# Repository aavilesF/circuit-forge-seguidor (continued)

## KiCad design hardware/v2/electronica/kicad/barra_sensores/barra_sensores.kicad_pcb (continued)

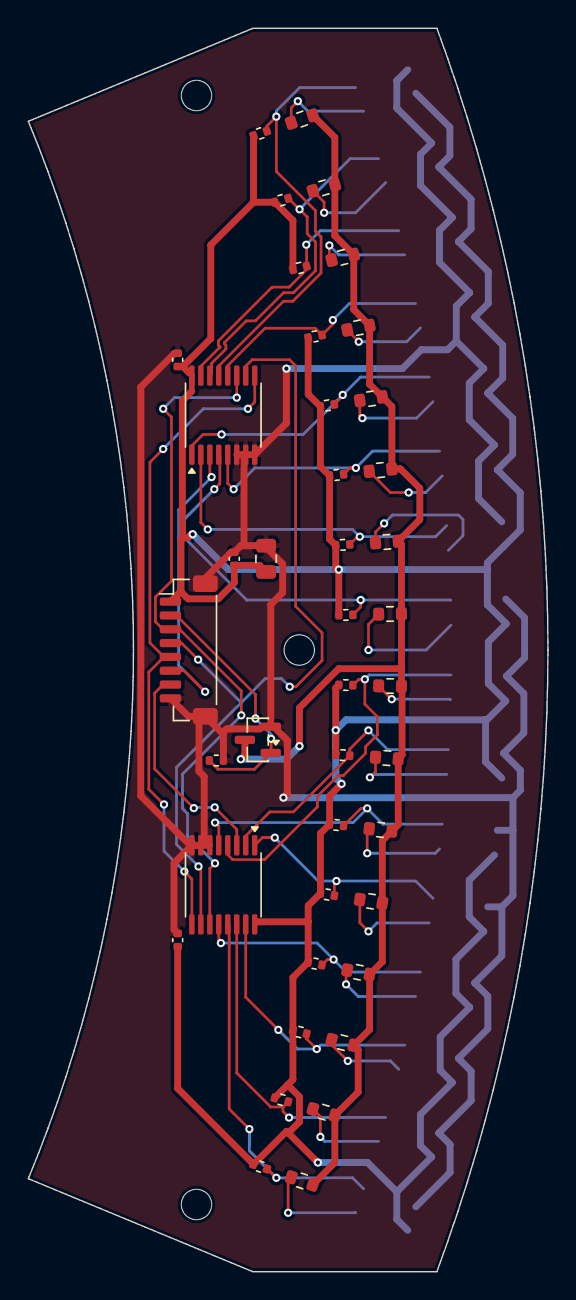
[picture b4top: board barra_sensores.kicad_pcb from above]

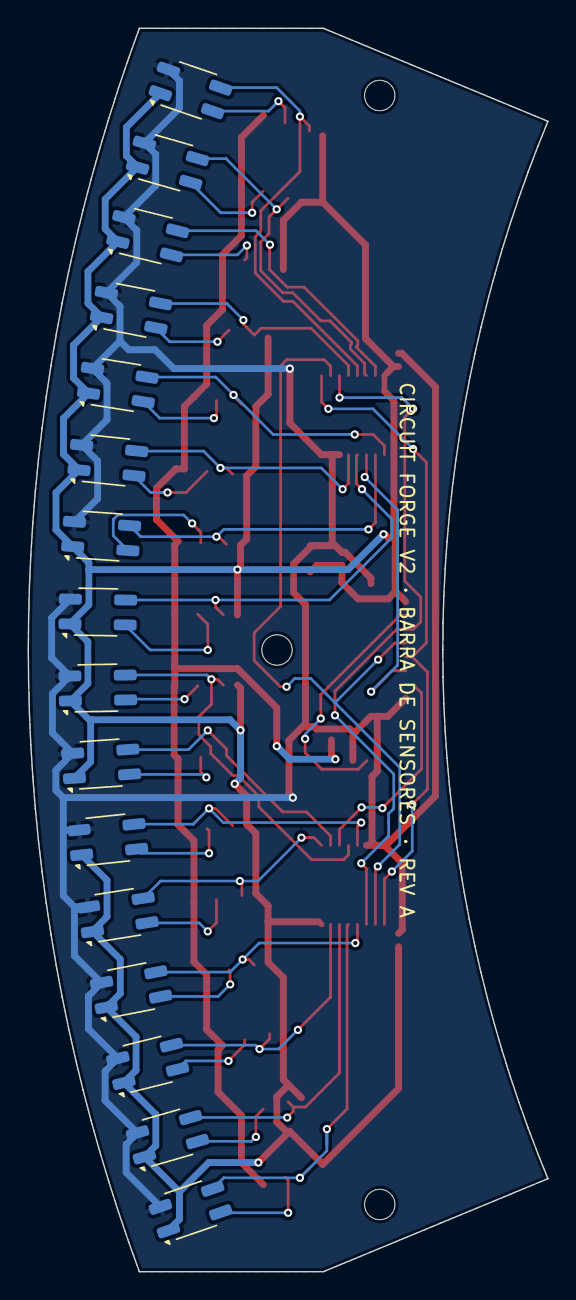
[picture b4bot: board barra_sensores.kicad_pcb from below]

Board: 2 copper layers, 37.6 x 90.0 mm, 60 parts (16 on the bottom side), 41 nets.

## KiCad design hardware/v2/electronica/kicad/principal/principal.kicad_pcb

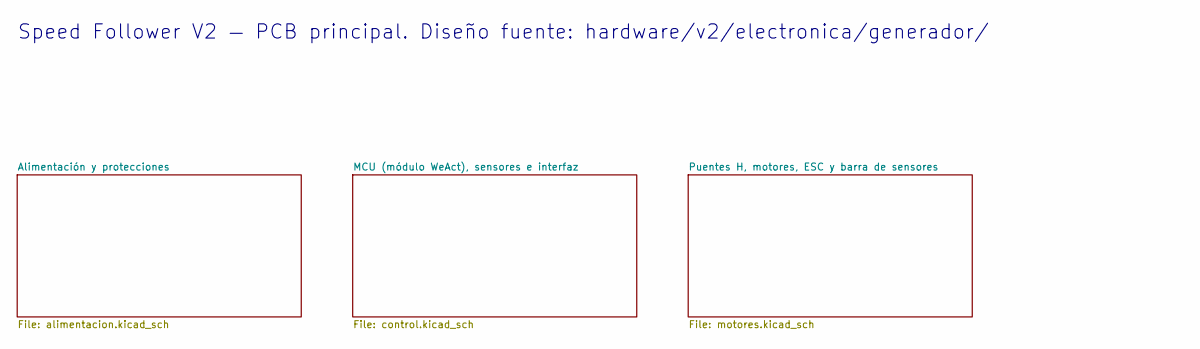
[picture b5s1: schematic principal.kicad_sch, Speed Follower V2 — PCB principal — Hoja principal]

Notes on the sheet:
Speed Follower V2 — PCB principal. Diseño fuente: hardware/v2/electronica/generador/

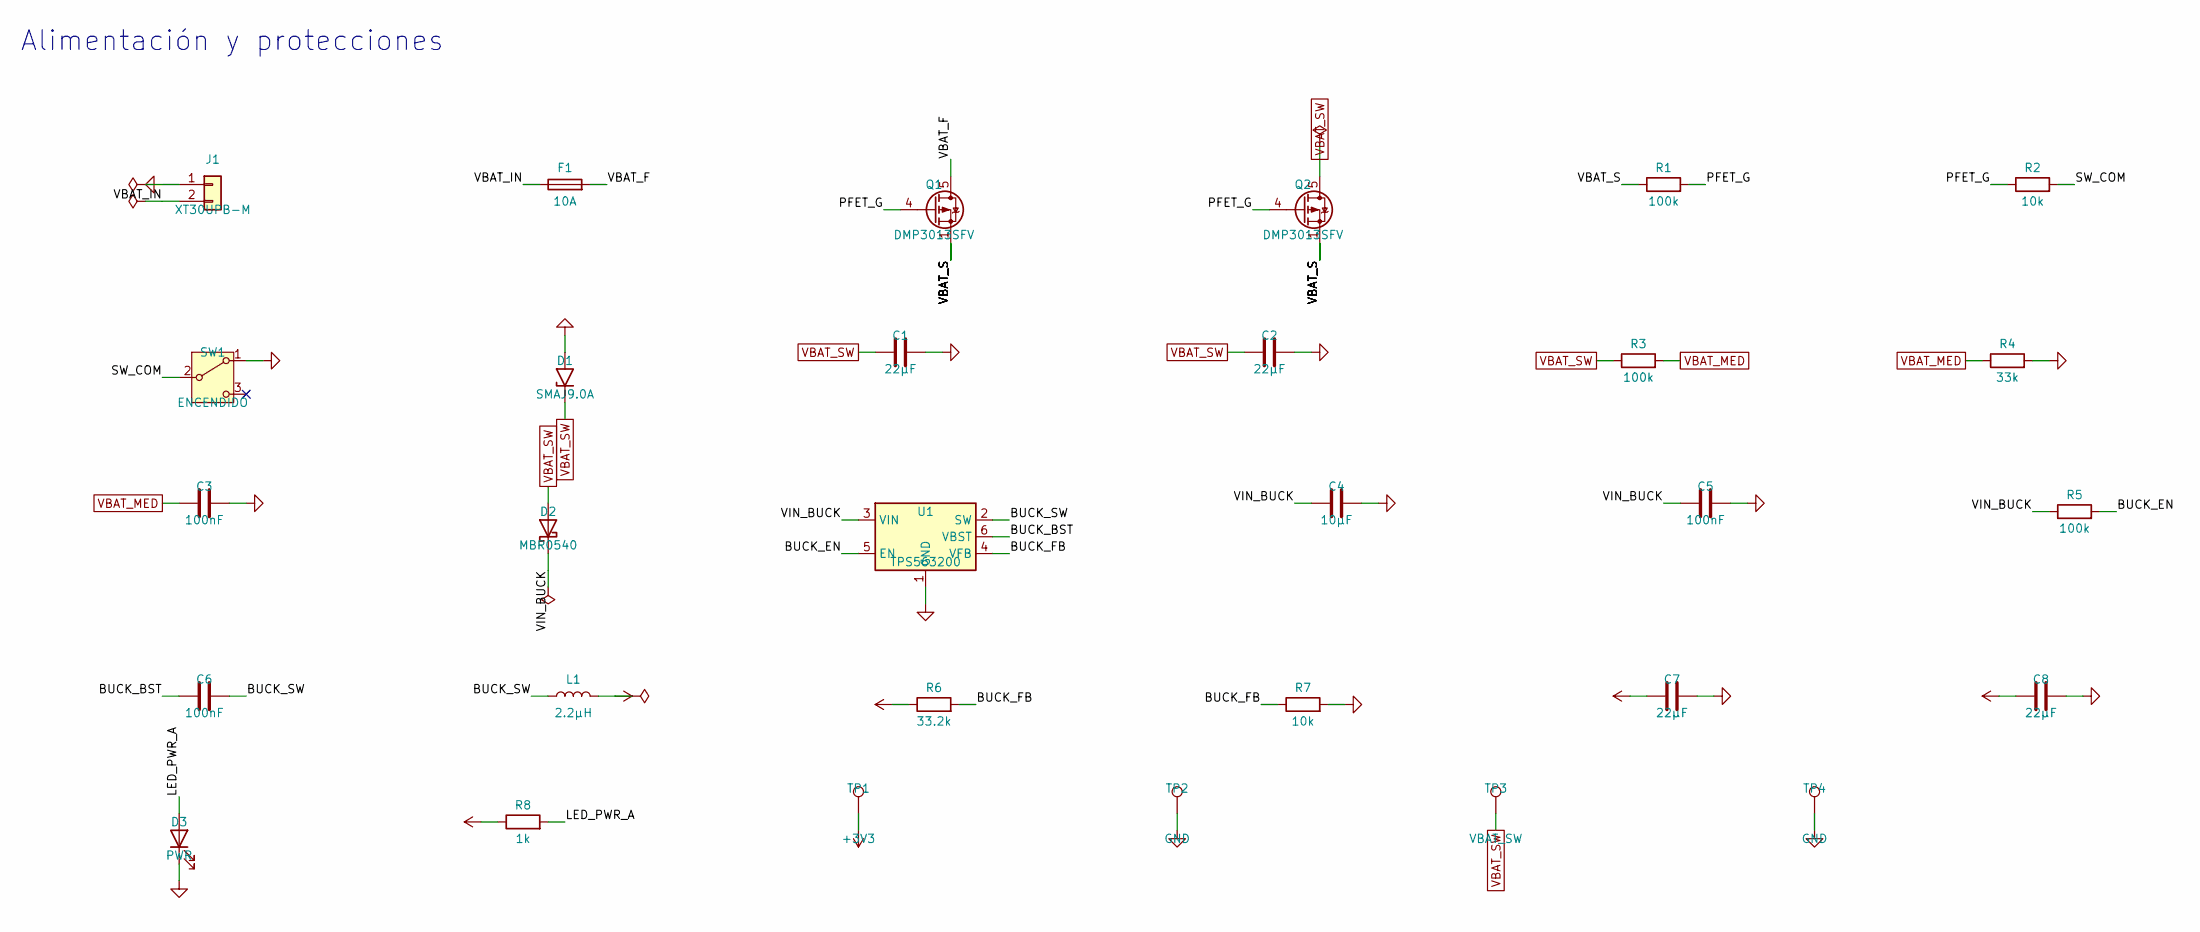
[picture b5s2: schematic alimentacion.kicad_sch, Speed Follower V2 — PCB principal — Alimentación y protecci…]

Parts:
C1, C2, C7, C8: 22µF; C_0805_2012Metric; MPN GRM21BR61E226ME44L
C3, C5, C6: 100nF; C_0402_1005Metric; MPN GRM155R71C104KA88D
C4: 10µF; C_0805_2012Metric; MPN GRM21BR61E106KA73L
D1: SMAJ9.0A; D_SMA; MPN SMAJ9.0A
D2: MBR0540; D_SOD-123; MPN MBR0540T1G
D3: PWR; LED_0603_1608Metric; MPN APT1608SGC
F1: 10A; Fuse_Blade_Mini_directSolder; MPN 0297010.WXNV
J1: XT30UPB-M; AMASS_XT30UPB-M_1x02_P5.0mm_Vertical; MPN XT30UPB-M
L1: 2.2µH; L_Wuerth_MAPI-4030; MPN 74438357022
Q1, Q2: DMP3013SFV; Diodes_PowerDI3333-8; MPN DMP3013SFV-7
R1, R3, R5: 100k; R_0402_1005Metric; MPN RC0402FR-07100KL
R2, R7: 10k; R_0402_1005Metric; MPN RC0402FR-0710KL
R4: 33k; R_0402_1005Metric; MPN RC0402FR-0733KL
R6: 33.2k; R_0402_1005Metric; MPN RC0402FR-0733K2L
R8: 1k; R_0402_1005Metric; MPN RC0402FR-071KL
SW1: ENCENDIDO; SW_Slide_SPDT_Angled_CK_OS102011MA1Q; MPN OS102011MA1QN1
TP1: +3V3; TestPoint_Pad_D1.0mm; MPN —
TP2, TP4: GND; TestPoint_Pad_D1.0mm; MPN —
TP3: VBAT_SW; TestPoint_Pad_D1.0mm; MPN —
U1: TPS563200; SOT-23-6; MPN TPS563200DDCR

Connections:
+3V3: C7.1, C8.1, L1.2, R6.1, R8.1, TP1.1; also elsewhere on the board
/Alimentación y protecciones/BUCK_BST: C6.1, U1.6 (VBST)
/Alimentación y protecciones/BUCK_EN: R5.2, U1.5 (EN)
/Alimentación y protecciones/BUCK_FB: R6.2, R7.1, U1.4 (VFB)
/Alimentación y protecciones/BUCK_SW: C6.2, L1.1, U1.2 (SW)
/Alimentación y protecciones/LED_PWR_A: D3.2 (A), R8.2
/Alimentación y protecciones/PFET_G: Q1.4 (G), Q2.4 (G), R1.2, R2.1
/Alimentación y protecciones/SW_COM: R2.2, SW1.2 (B)
/Alimentación y protecciones/VBAT_F: F1.2, Q1.5 (D)
/Alimentación y protecciones/VBAT_IN: F1.1, J1.2
/Alimentación y protecciones/VBAT_S: Q1.1 (S), Q1.2 (S), Q1.3 (S), Q2.1 (S), Q2.2 (S), Q2.3 (S), R1.1
/Alimentación y protecciones/VIN_BUCK: C4.1, C5.1, D2.1 (K), R5.1, U1.3 (VIN)
GND: C1.2, C2.2, C3.2, C4.2, C5.2, C7.2, C8.2, D1.2 (A2), D3.1 (K), J1.1, R4.2, R7.2, SW1.1 (A), TP2.1, TP4.1, U1.1 (GND); also elsewhere on the board
VBAT_MED: C3.1, R3.2, R4.1; also elsewhere on the board
VBAT_SW: C1.1, C2.1, D1.1 (A1), D2.2 (A), Q2.5 (D), R3.1, TP3.1; also elsewhere on the board

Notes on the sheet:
Alimentación y protecciones

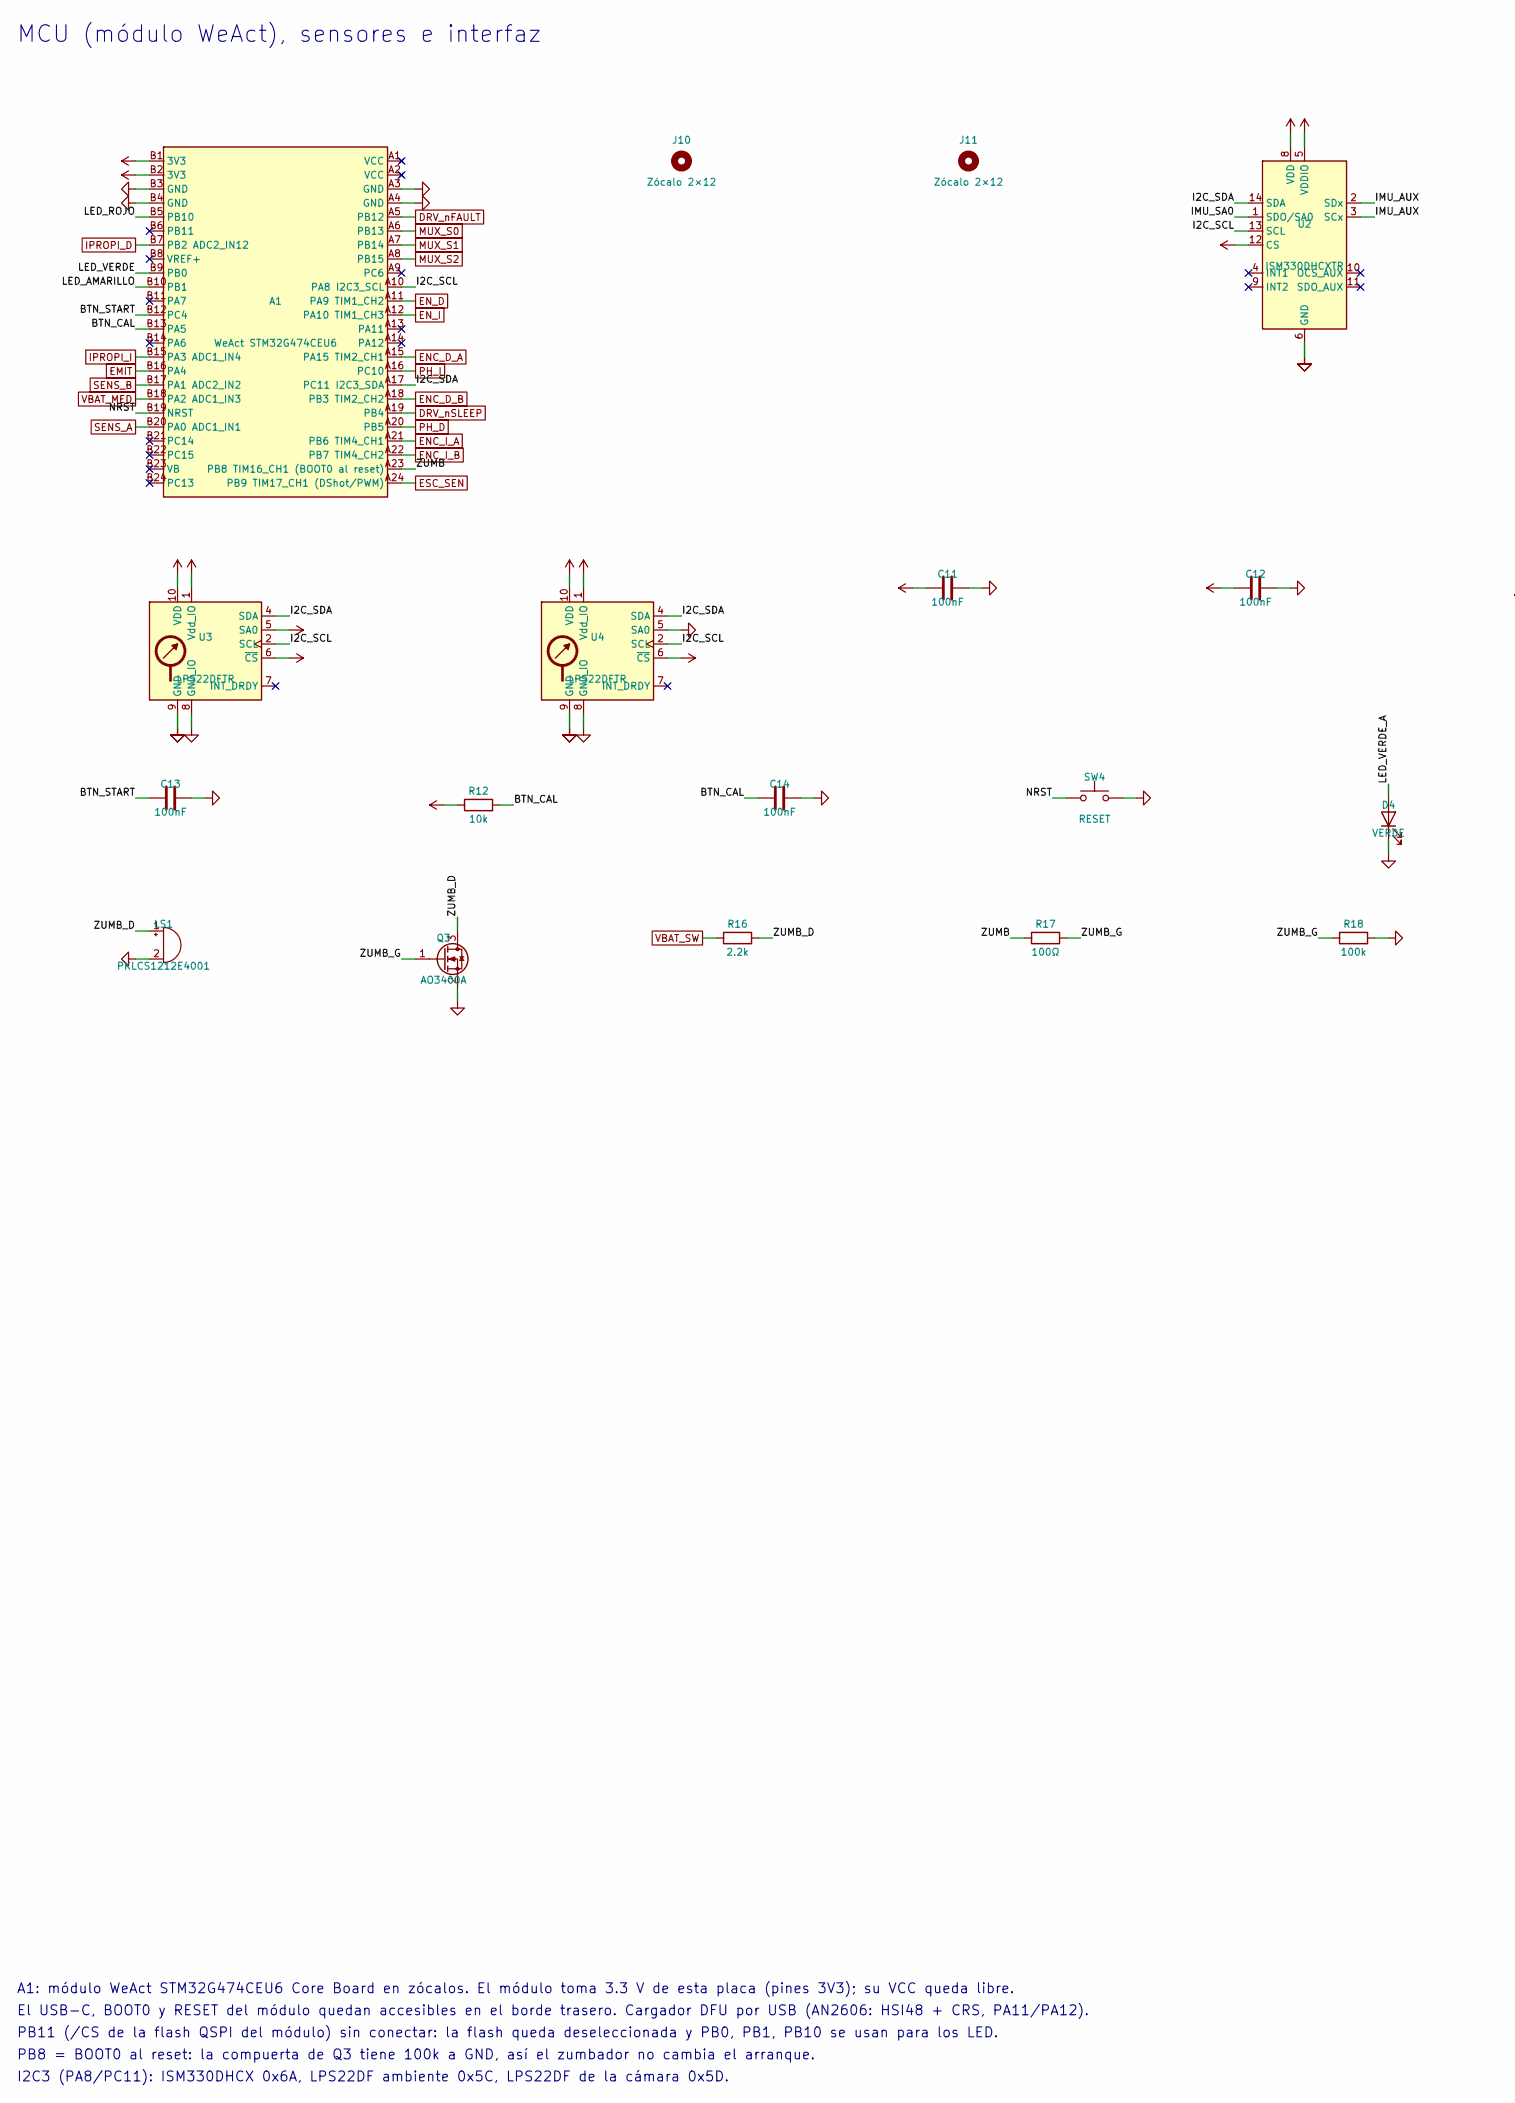
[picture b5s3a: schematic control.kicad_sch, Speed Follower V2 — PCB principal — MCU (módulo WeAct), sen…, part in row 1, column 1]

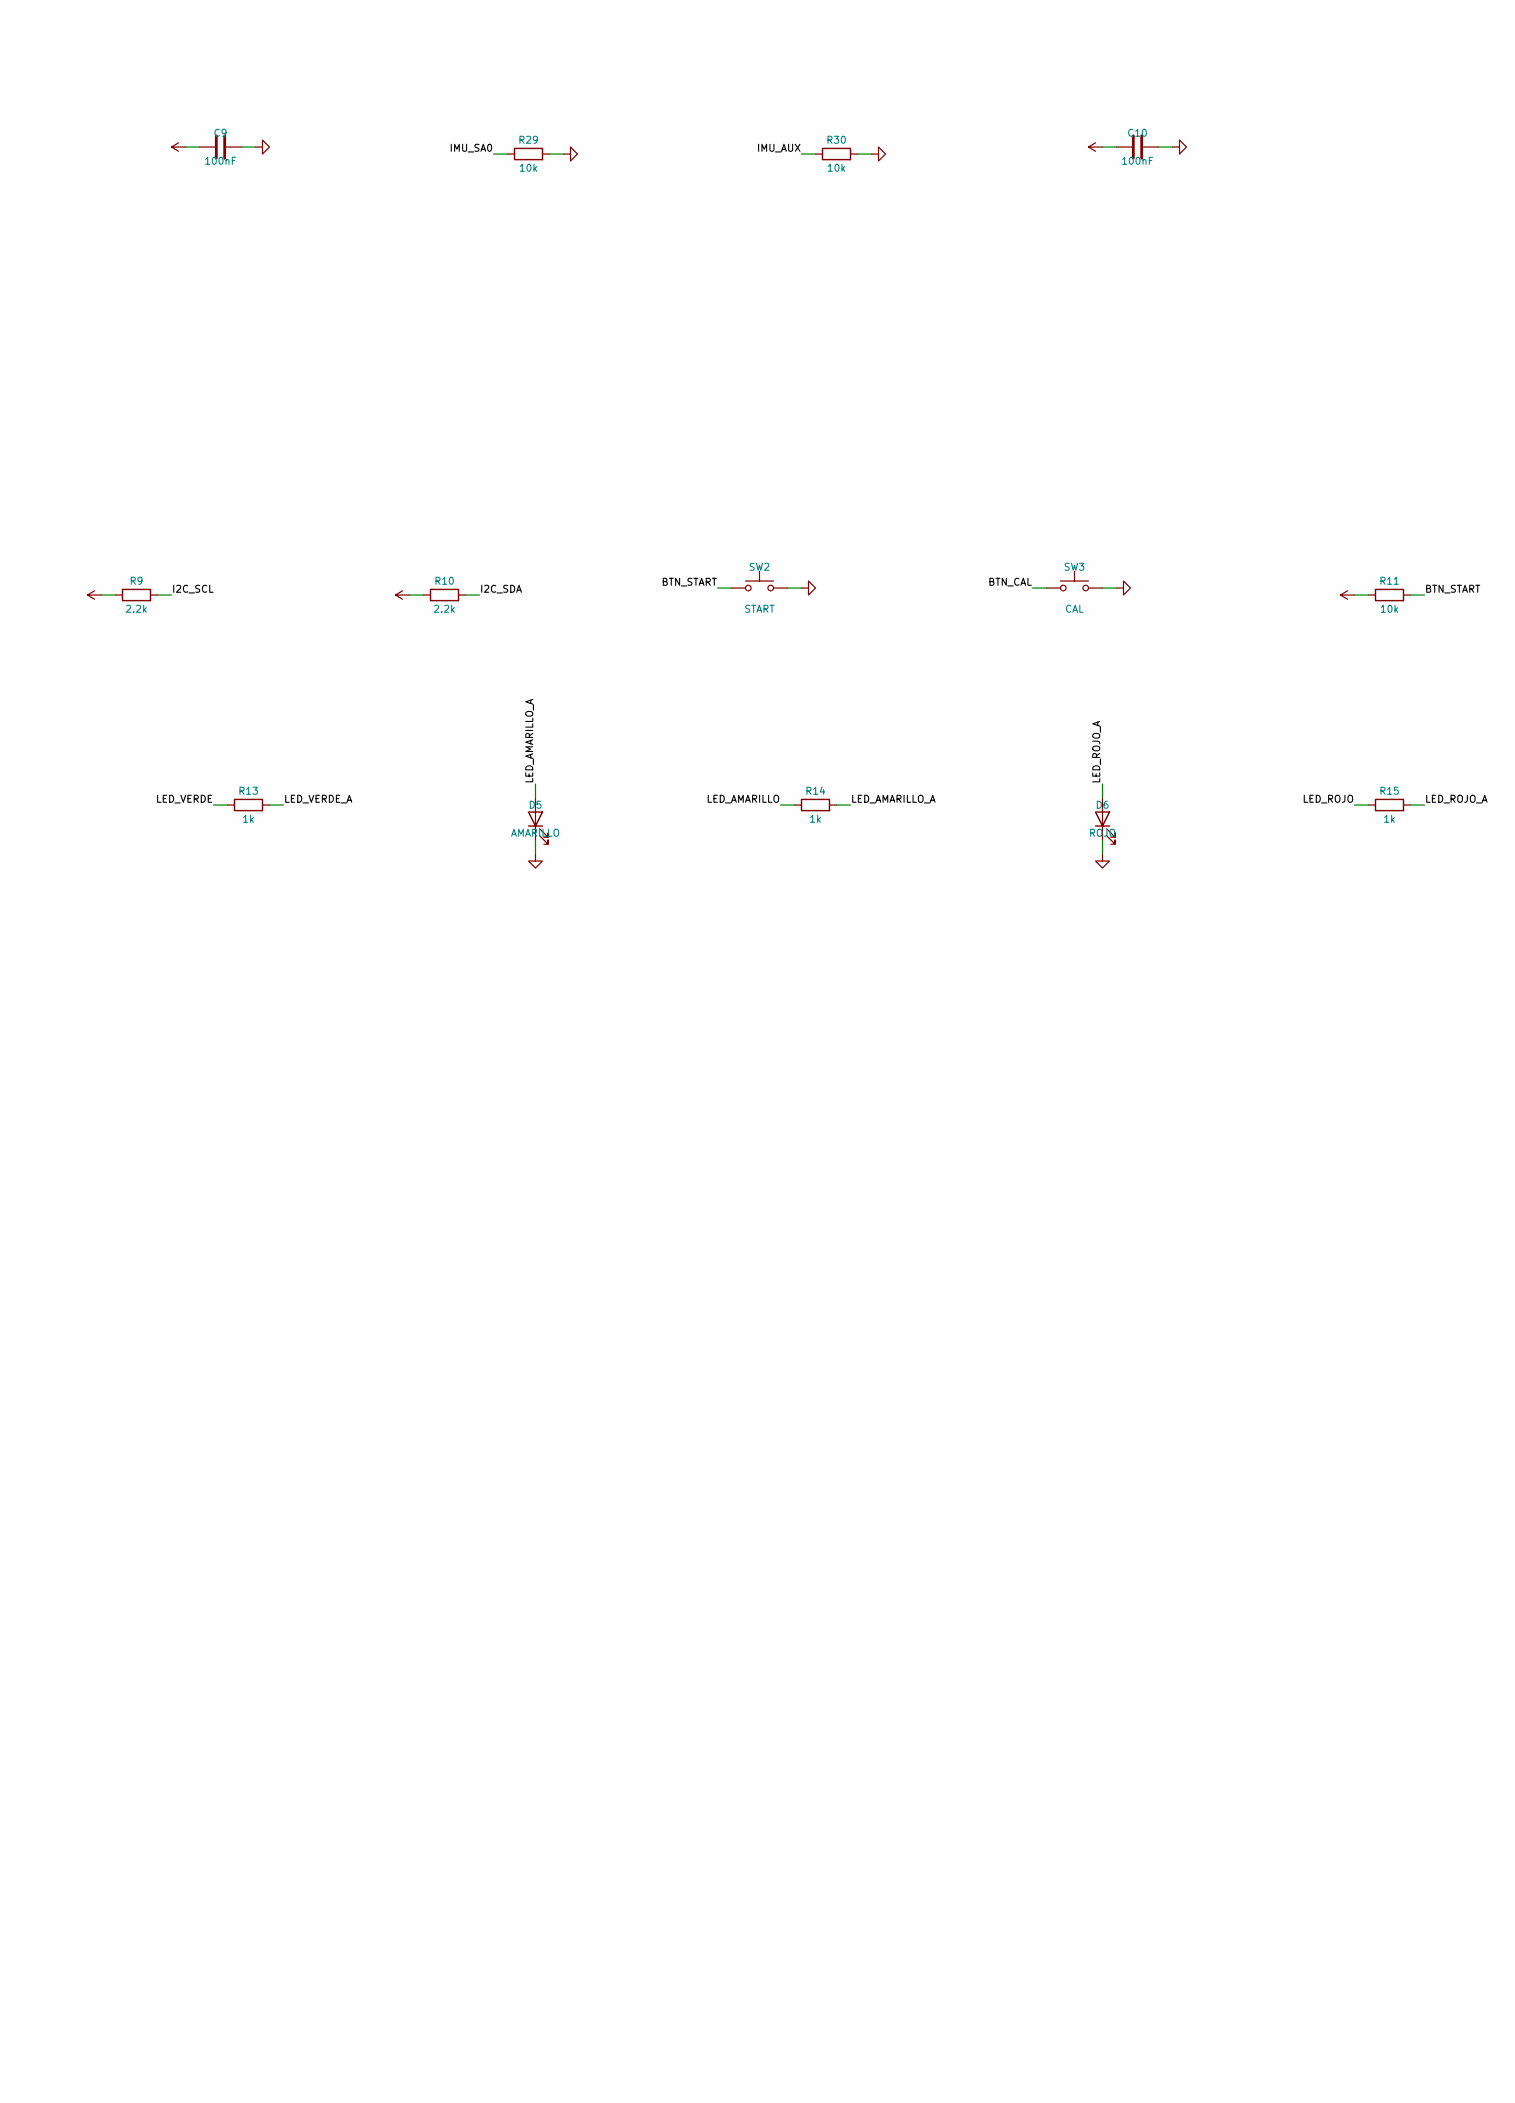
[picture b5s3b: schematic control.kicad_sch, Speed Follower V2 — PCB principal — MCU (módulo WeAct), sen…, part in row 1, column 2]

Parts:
A1: WeAct STM32G474CEU6; WeAct_STM32G474_CoreBoard_Zocalo; MPN STM32G474CEU6 Core Board V1.0
C9, C10, C11, C12, C13, C14: 100nF; C_0402_1005Metric; MPN GRM155R71C104KA88D
D4: VERDE; LED_0603_1608Metric; MPN APT1608SGC
D5: AMARILLO; LED_0603_1608Metric; MPN APT1608YC
D6: ROJO; LED_0603_1608Metric; MPN APT1608EC
J10, J11: Zócalo 2×12; MPN Zócalo hembra 2×12, paso 2.54 mm, 8.5 m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
LS1: PKLCS1212E4001; Buzzer_Murata_PKLCS1212E; MPN PKLCS1212E4001-R1
Q3: AO3400A; SOT-23; MPN AO3400A
R9, R10, R16: 2.2k; R_0402_1005Metric; MPN RC0402FR-072K2L
R11, R12, R29, R30: 10k; R_0402_1005Metric; MPN RC0402FR-0710KL
R13, R14, R15: 1k; R_0402_1005Metric; MPN RC0402FR-071KL
R17: 100Ω; R_0402_1005Metric; MPN RC0402FR-07100RL
R18: 100k; R_0402_1005Metric; MPN RC0402FR-07100KL
SW2: START; SW_SPST_Omron_B3FS-100xP; MPN B3FS-1000P
SW3: CAL; SW_SPST_Omron_B3FS-100xP; MPN B3FS-1000P
SW4: RESET; SW_SPST_B3U-1000P; MPN B3U-1000P
U2: ISM330DHCXTR; LGA-14_3x2.5mm_P0.5mm_LayoutBorder3x4y; MPN ISM330DHCXTR
U3, U4: LPS22DFTR; ST_HLGA-10_2x2mm_P0.5mm_LayoutBorder3x2y; MPN LPS22DFTR

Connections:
+3V3: A1.B1 (3V3), A1.B2 (3V3), C9.1, C10.1, C11.1, C12.1, R9.1, R10.1, R11.1, R12.1, U2.5 (VDDIO), U2.8 (VDD), U2.12 (CS), U3.1 (Vdd_IO), U3.5 (SA0), U3.6 (~CS), U3.10 (VDD), U4.1 (Vdd_IO), U4.6 (~CS), U4.10 (VDD); also elsewhere on the board
/MCU (módulo WeAct), sensores e interfaz/BTN_CAL: A1.B13 (PA5), C14.1, R12.2, SW3.1
/MCU (módulo WeAct), sensores e interfaz/BTN_START: A1.B12 (PC4), C13.1, R11.2, SW2.1
/MCU (módulo WeAct), sensores e interfaz/I2C_SCL: A1.A10 (PA8 I2C3_SCL), R9.2, U2.13 (SCL), U3.2 (SCL), U4.2 (SCL)
/MCU (módulo WeAct), sensores e interfaz/I2C_SDA: A1.A17 (PC11 I2C3_SDA), R10.2, U2.14 (SDA), U3.4 (SDA), U4.4 (SDA)
/MCU (módulo WeAct), sensores e interfaz/IMU_AUX: R30.1, U2.2 (SDx), U2.3 (SCx)
/MCU (módulo WeAct), sensores e interfaz/IMU_SA0: R29.1, U2.1 (SDO/SA0)
/MCU (módulo WeAct), sensores e interfaz/LED_AMARILLO: A1.B10 (PB1), R14.1
/MCU (módulo WeAct), sensores e interfaz/LED_AMARILLO_A: D5.2 (A), R14.2
/MCU (módulo WeAct), sensores e interfaz/LED_ROJO: A1.B5 (PB10), R15.1
/MCU (módulo WeAct), sensores e interfaz/LED_ROJO_A: D6.2 (A), R15.2
/MCU (módulo WeAct), sensores e interfaz/LED_VERDE: A1.B9 (PB0), R13.1
/MCU (módulo WeAct), sensores e interfaz/LED_VERDE_A: D4.2 (A), R13.2
/MCU (módulo WeAct), sensores e interfaz/NRST: A1.B19 (NRST), SW4.1
/MCU (módulo WeAct), sensores e interfaz/ZUMB: A1.A23 (PB8 TIM16_CH1 (BOOT0 al reset)), R17.1
/MCU (módulo WeAct), sensores e interfaz/ZUMB_D: LS1.1 (+), Q3.3 (D), R16.2
/MCU (módulo WeAct), sensores e interfaz/ZUMB_G: Q3.1 (G), R17.2, R18.1
DRV_nFAULT: A1.A5 (PB12); also elsewhere on the board
DRV_nSLEEP: A1.A19 (PB4); also elsewhere on the board
EMIT: A1.B16 (PA4); also elsewhere on the board
ENC_D_A: A1.A15 (PA15 TIM2_CH1); also elsewhere on the board
ENC_D_B: A1.A18 (PB3 TIM2_CH2); also elsewhere on the board
ENC_I_A: A1.A21 (PB6 TIM4_CH1); also elsewhere on the board
ENC_I_B: A1.A22 (PB7 TIM4_CH2); also elsewhere on the board
EN_D: A1.A11 (PA9 TIM1_CH2); also elsewhere on the board
EN_I: A1.A12 (PA10 TIM1_CH3); also elsewhere on the board
ESC_SEN: A1.A24 (PB9 TIM17_CH1 (DShot/PWM)); also elsewhere on the board
GND: A1.A3 (GND), A1.A4 (GND), A1.B3 (GND), A1.B4 (GND), C9.2, C10.2, C11.2, C12.2, C13.2, C14.2, D4.1 (K), D5.1 (K), D6.1 (K), LS1.2 (-), Q3.2 (S), R18.2, R29.2, R30.2, SW2.2, SW3.2, SW4.2, U2.6 (GND), U2.7 (GND), U3.3 (GND), U3.8 (GND_IO), U3.9 (GND), U4.3 (GND), U4.5 (SA0), U4.8 (GND_IO), U4.9 (GND); also elsewhere on the board
IPROPI_D: A1.B7 (PB2 ADC2_IN12); also elsewhere on the board
IPROPI_I: A1.B15 (PA3 ADC1_IN4); also elsewhere on the board
MUX_S0: A1.A6 (PB13); also elsewhere on the board
MUX_S1: A1.A7 (PB14); also elsewhere on the board
MUX_S2: A1.A8 (PB15); also elsewhere on the board
PH_D: A1.A20 (PB5); also elsewhere on the board
PH_I: A1.A16 (PC10); also elsewhere on the board
SENS_A: A1.B20 (PA0 ADC1_IN1); also elsewhere on the board
SENS_B: A1.B17 (PA1 ADC2_IN2); also elsewhere on the board
VBAT_MED: A1.B18 (PA2 ADC1_IN3); also elsewhere on the board
VBAT_SW: R16.1; also elsewhere on the board

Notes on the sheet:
MCU (módulo WeAct), sensores e interfaz
A1: módulo WeAct STM32G474CEU6 Core Board en zócalos. El módulo toma 3.3 V de esta placa (pines 3V3); su VCC queda libre.
El USB-C, BOOT0 y RESET del módulo quedan accesibles en el borde trasero. Cargador DFU por USB (AN2606: HSI48 + CRS, PA11/PA12).
PB11 (/CS de la flash QSPI del módulo) sin conectar: la flash queda deseleccionada y PB0, PB1, PB10 se usan para los LED.
PB8 = BOOT0 al reset: la compuerta de Q3 tiene 100k a GND, así el zumbador no cambia el arranque.
I2C3 (PA8/PC11): ISM330DHCX 0x6A, LPS22DF ambiente 0x5C, LPS22DF de la cámara 0x5D.

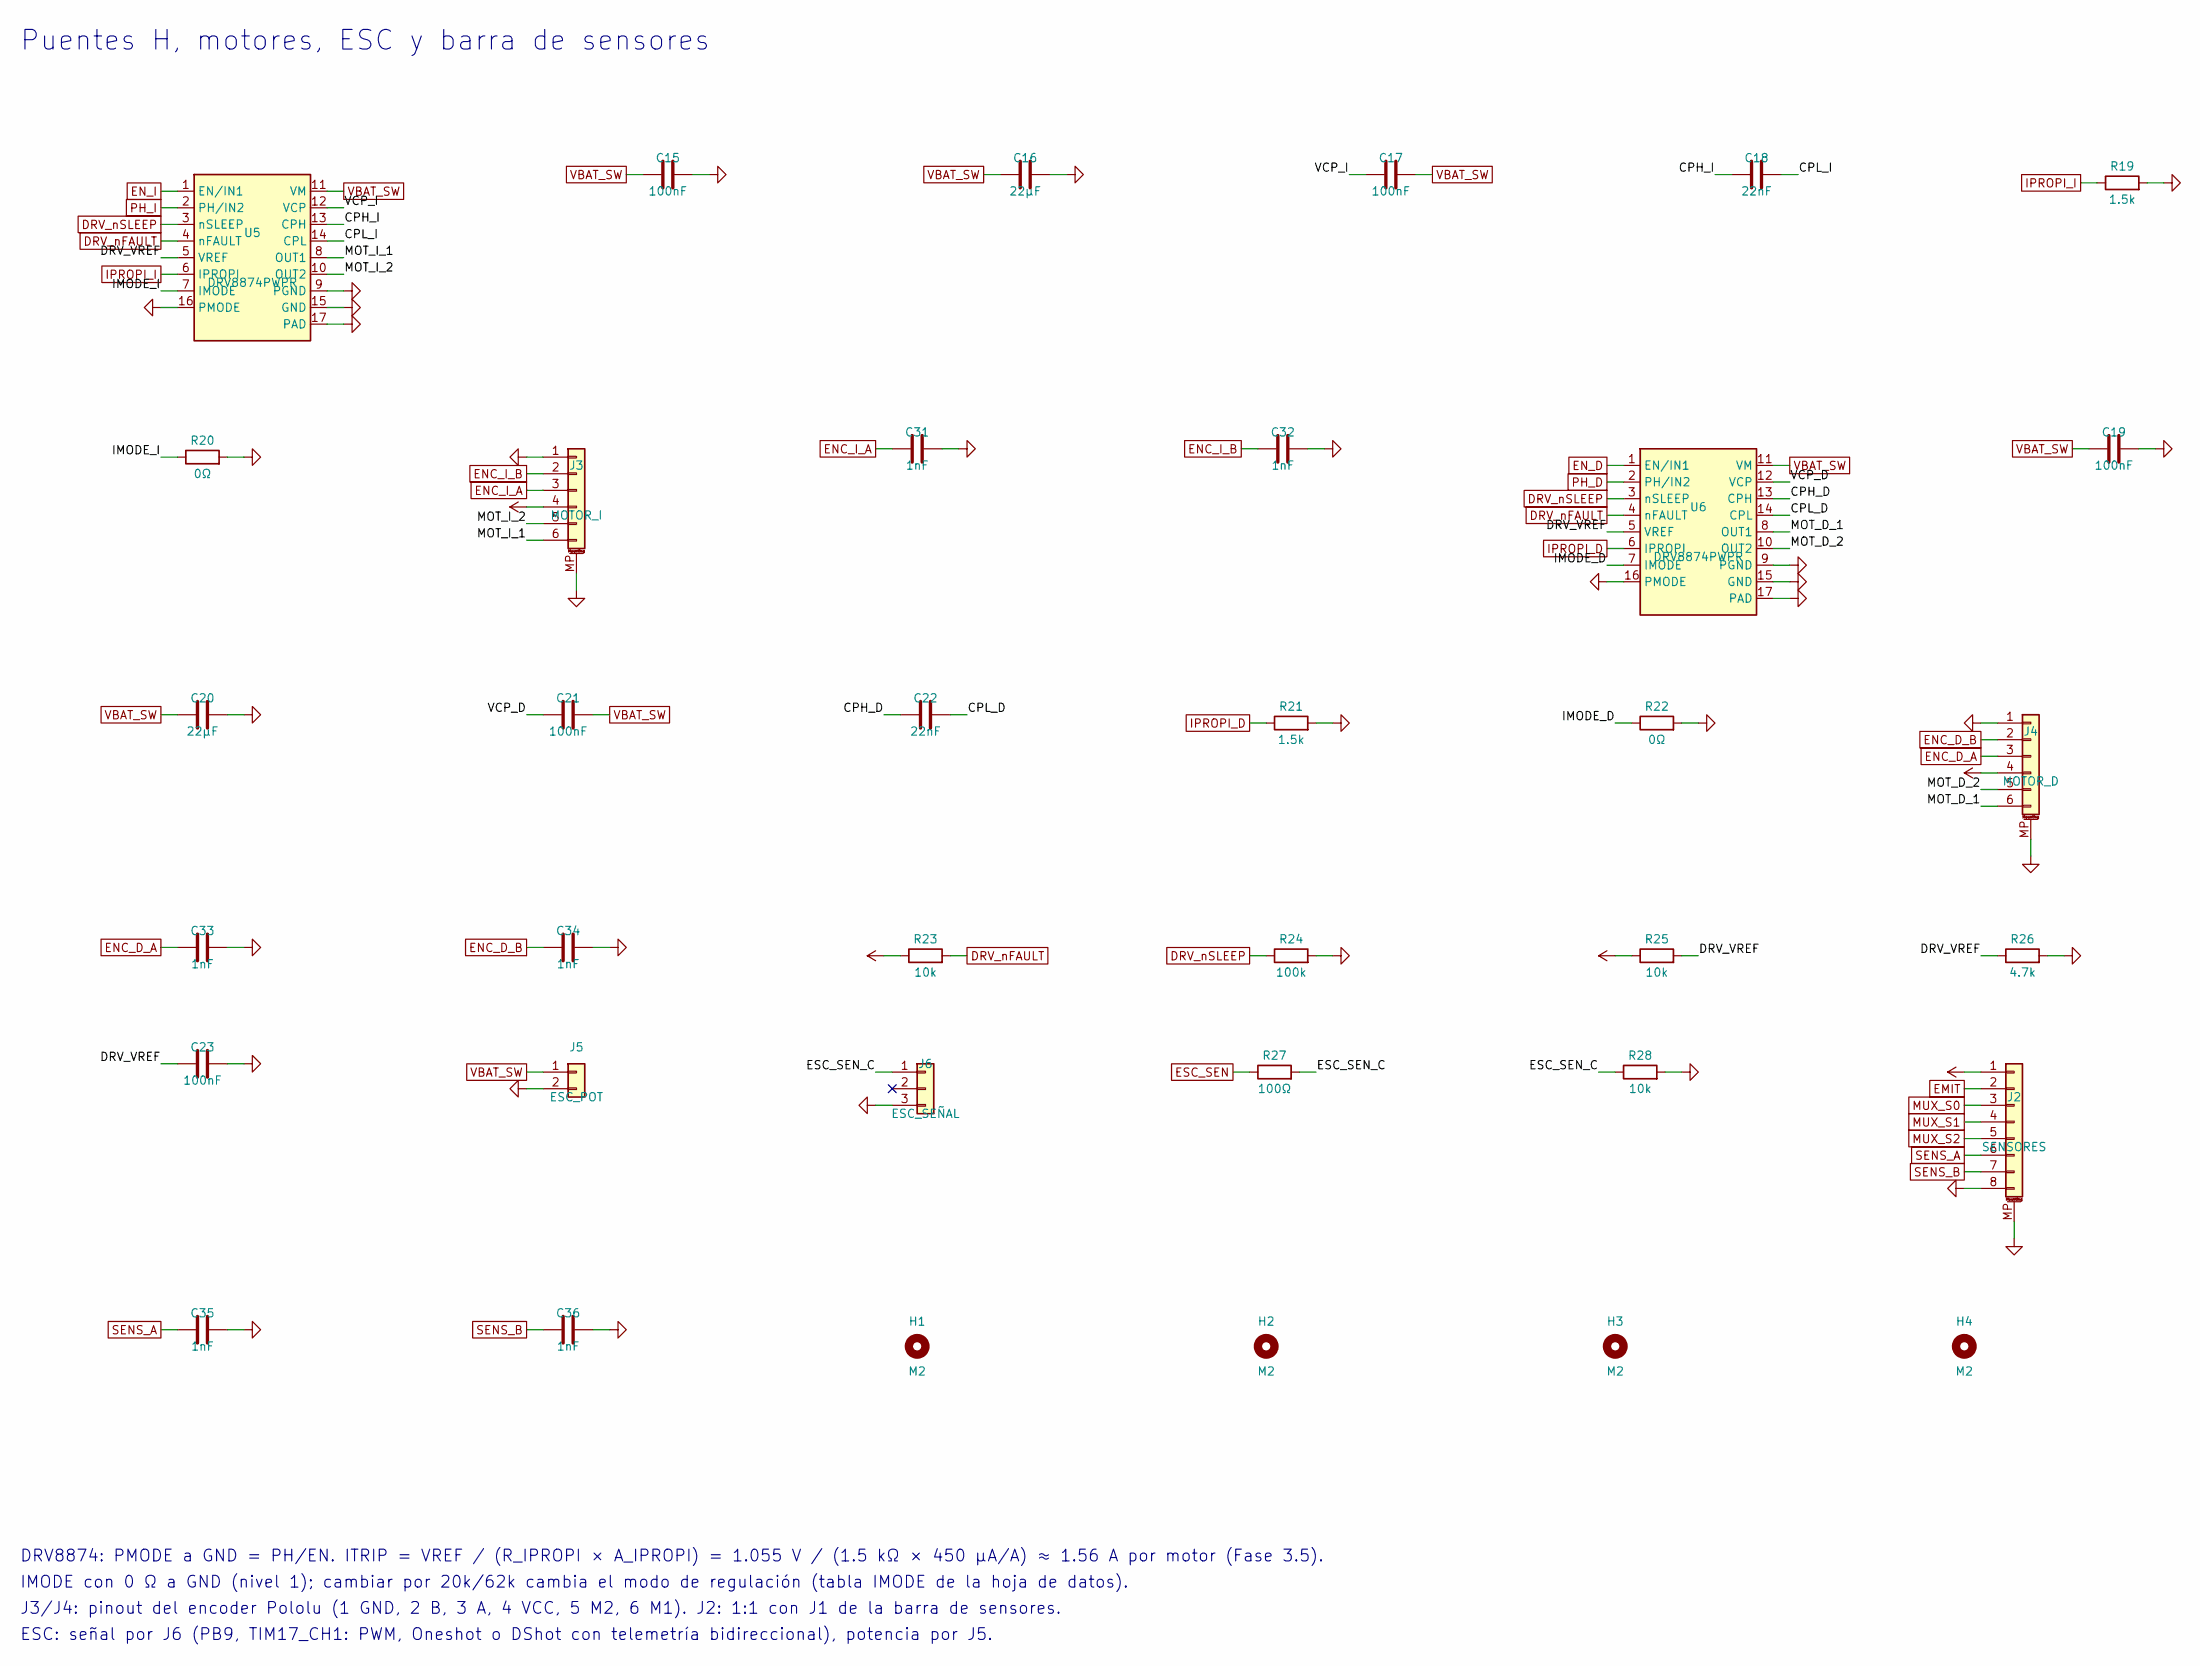
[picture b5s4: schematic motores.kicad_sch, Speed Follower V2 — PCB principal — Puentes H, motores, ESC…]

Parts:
C15, C17, C19, C21, C23: 100nF; C_0402_1005Metric; MPN GRM155R71C104KA88D
C16, C20: 22µF; C_0805_2012Metric; MPN GRM21BR61E226ME44L
C18, C22: 22nF; C_0402_1005Metric; MPN GRM155R71H223KA12D
C31, C32, C33, C34, C35, C36: 1nF; C_0402_1005Metric; MPN GRM155R71H102KA01D
H1, H2, H3, H4: M2; MountingHole_2.2mm_M2; MPN —
J2: SENSORES; JST_SH_BM08B-SRSS-TB_1x08-1MP_P1.00mm_Vertical; MPN BM08B-SRSS-TB
J3: MOTOR_I; JST_SH_BM06B-SRSS-TB_1x06-1MP_P1.00mm_Vertical; MPN BM06B-SRSS-TB
J4: MOTOR_D; JST_SH_BM06B-SRSS-TB_1x06-1MP_P1.00mm_Vertical; MPN BM06B-SRSS-TB
J5: ESC_POT; SolderWire-0.5sqmm_1x02_P4.6mm_D0.9mm_OD2.1mm; MPN —
J6: ESC_SEÑAL; PinHeader_1x03_P2.54mm_Vertical; MPN Cabecera macho 1×3, paso 2.54 mm (númer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
R19, R21: 1.5k; R_0402_1005Metric; MPN RC0402FR-071K5L
R20, R22: 0Ω; R_0402_1005Metric; MPN RC0402JR-070RL
R23, R25, R28: 10k; R_0402_1005Metric; MPN RC0402FR-0710KL
R24: 100k; R_0402_1005Metric; MPN RC0402FR-07100KL
R26: 4.7k; R_0402_1005Metric; MPN RC0402FR-074K7L
R27: 100Ω; R_0402_1005Metric; MPN RC0402FR-07100RL
U5, U6: DRV8874PWPR; HTSSOP-16-1EP_4.4x5mm_P0.65mm_EP3.4x5mm_Mask2.46x2.31mm; MPN DRV8874PWPR

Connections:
+3V3: J2.1, J3.4, J4.4, R23.1, R25.1; also elsewhere on the board
/Puentes H, motores, ESC y barra de sensores/CPH_D: C22.1, U6.13 (CPH)
/Puentes H, motores, ESC y barra de sensores/CPH_I: C18.1, U5.13 (CPH)
/Puentes H, motores, ESC y barra de sensores/CPL_D: C22.2, U6.14 (CPL)
/Puentes H, motores, ESC y barra de sensores/CPL_I: C18.2, U5.14 (CPL)
/Puentes H, motores, ESC y barra de sensores/DRV_VREF: C23.1, R25.2, R26.1, U5.5 (VREF), U6.5 (VREF)
/Puentes H, motores, ESC y barra de sensores/ESC_SEN_C: J6.1, R27.2, R28.1
/Puentes H, motores, ESC y barra de sensores/IMODE_D: R22.1, U6.7 (IMODE)
/Puentes H, motores, ESC y barra de sensores/IMODE_I: R20.1, U5.7 (IMODE)
/Puentes H, motores, ESC y barra de sensores/MOT_D_1: J4.6, U6.8 (OUT1)
/Puentes H, motores, ESC y barra de sensores/MOT_D_2: J4.5, U6.10 (OUT2)
/Puentes H, motores, ESC y barra de sensores/MOT_I_1: J3.6, U5.8 (OUT1)
/Puentes H, motores, ESC y barra de sensores/MOT_I_2: J3.5, U5.10 (OUT2)
/Puentes H, motores, ESC y barra de sensores/VCP_D: C21.1, U6.12 (VCP)
/Puentes H, motores, ESC y barra de sensores/VCP_I: C17.1, U5.12 (VCP)
DRV_nFAULT: R23.2, U5.4 (nFAULT), U6.4 (nFAULT); also elsewhere on the board
DRV_nSLEEP: R24.1, U5.3 (nSLEEP), U6.3 (nSLEEP); also elsewhere on the board
EMIT: J2.2; also elsewhere on the board
ENC_D_A: C33.1, J4.3; also elsewhere on the board
ENC_D_B: C34.1, J4.2; also elsewhere on the board
ENC_I_A: C31.1, J3.3; also elsewhere on the board
ENC_I_B: C32.1, J3.2; also elsewhere on the board
EN_D: U6.1 (EN/IN1); also elsewhere on the board
EN_I: U5.1 (EN/IN1); also elsewhere on the board
ESC_SEN: R27.1; also elsewhere on the board
GND: C15.2, C16.2, C19.2, C20.2, C23.2, C31.2, C32.2, C33.2, C34.2, C35.2, C36.2, J2.8, J2.MP (MountPin), J3.1, J3.MP (MountPin), J4.1, J4.MP (MountPin), J5.2, J6.3, R19.2, R20.2, R21.2, R22.2, R24.2, R26.2, R28.2, U5.9 (PGND), U5.15 (GND), U5.16 (PMODE), U5.17 (PAD), U6.9 (PGND), U6.15 (GND), U6.16 (PMODE), U6.17 (PAD); also elsewhere on the board
IPROPI_D: R21.1, U6.6 (IPROPI); also elsewhere on the board
IPROPI_I: R19.1, U5.6 (IPROPI); also elsewhere on the board
MUX_S0: J2.3; also elsewhere on the board
MUX_S1: J2.4; also elsewhere on the board
MUX_S2: J2.5; also elsewhere on the board
PH_D: U6.2 (PH/IN2); also elsewhere on the board
PH_I: U5.2 (PH/IN2); also elsewhere on the board
SENS_A: C35.1, J2.6; also elsewhere on the board
SENS_B: C36.1, J2.7; also elsewhere on the board
VBAT_SW: C15.1, C16.1, C17.2, C19.1, C20.1, C21.2, J5.1, U5.11 (VM), U6.11 (VM); also elsewhere on the board

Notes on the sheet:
Puentes H, motores, ESC y barra de sensores
DRV8874: PMODE a GND = PH/EN. ITRIP = VREF / (R_IPROPI × A_IPROPI) = 1.055 V / (1.5 kΩ × 450 µA/A) ≈ 1.56 A por motor (Fase 3.5).
IMODE con 0 Ω a GND (nivel 1); cambiar por 20k/62k cambia el modo de regulación (tabla IMODE de la hoja de datos).
J3/J4: pinout del encoder Pololu (1 GND, 2 B, 3 A, 4 VCC, 5 M2, 6 M1). J2: 1:1 con J1 de la barra de sensores.
ESC: señal por J6 (PB9, TIM17_CH1: PWM, Oneshot o DShot con telemetría bidireccional), potencia por J5.
